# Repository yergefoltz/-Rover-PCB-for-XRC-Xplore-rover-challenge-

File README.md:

# -Rover-PCB-for-XRC-Xplore-rover-challenge-
My first PCB made for rover challenge at my university was designed to connect all electronics in our small rover.

1.	Main Purpose:
I decided to design our PCB solely for connections and routing logic signals between our components. The power supply lines for the servo and DC motors will not run through the board in order to avoid significant electrical noise that could interfere with the operation of the logic components.
2.	Brain – Master – Slaves 
The Raspberry Pi will not be fully mounted on the PCB; only a header with 20 pins will be included.
The same approach will be used for the Arduino master.
For the Arduino slaves, there will be dedicated spots on the PCB, allowing them to be mounted and removed as needed.
This design choice was made to avoid wasting space on the board and to keep it compact.
An important clarification: the appropriate resistors have been placed on the PCB to ensure proper logic operation.
Pull-up resistors are used for UART, along with a voltage divider between the Arduino master and the other components to ensure correct signal transmission.

Some additional components were placed to make the work of arduinos proper:

The ferrite bead (FB1) filters high-frequency noise on the power line.
The 100nF capacitor suppresses fast voltage spikes near the Arduino.
The 4.7µF capacitor smooths slower voltage drops.
Together, they stabilize the power and reduce noise from motors and servos.
This setup helps prevent glitches and random resets.
3.	More about Slaves…
Overall, we will have four Arduino slaves, each with its own specific role. Slaves #1 and #2 will handle rover control. Each of them will receive signals from the master (which in turn receives them from the Raspberry Pi), and will control the motors in parallel pairs via a driver (left front & rear + right front & rear), as well as one servo motor each.
This approach was chosen to improve the rover’s turning performance, where the servo motors will be especially useful.
Slave #3 will be used as a mini controller for the robotic arm, managing five servo motors, as well as two additional servos used in the LiDAR system. In total, it will control seven servo motors.
A dedicated slave was assigned for this purpose to avoid overloading the system and adding extra strain to the other components.

The final slave, #4, will manage all the sensors in the system and transmit the data to the appropriate modules.

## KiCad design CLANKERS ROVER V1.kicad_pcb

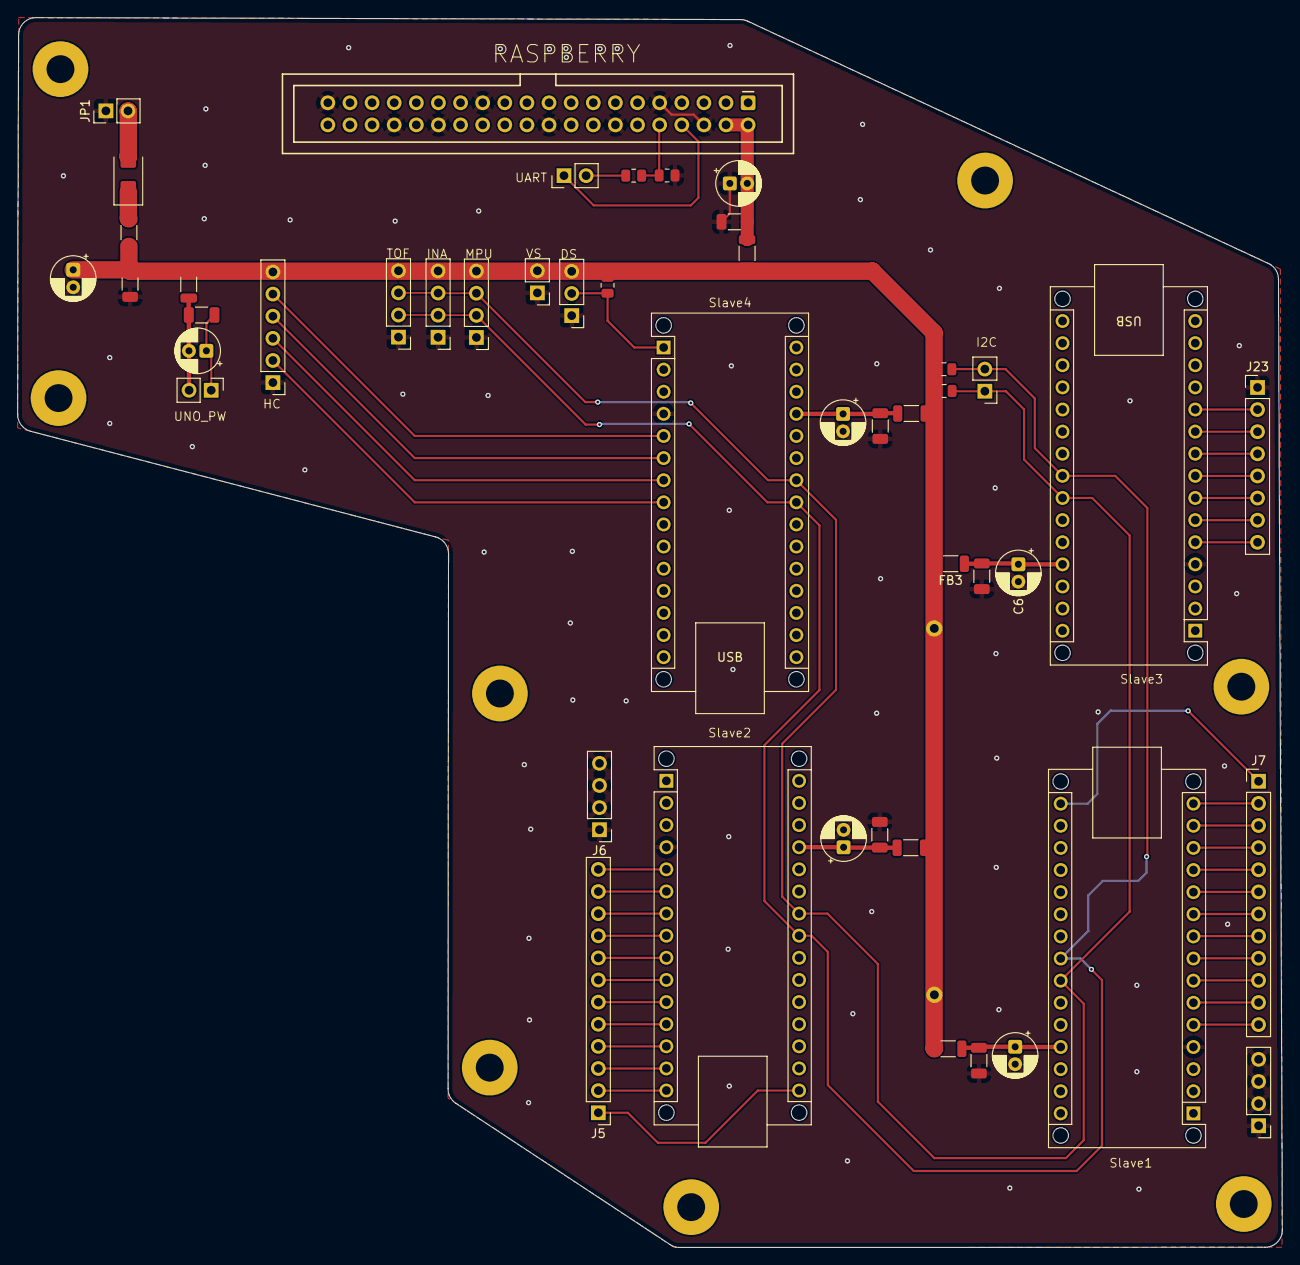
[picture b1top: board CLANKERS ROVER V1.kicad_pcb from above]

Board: 4 copper layers, 145.2 x 141.2 mm, 49 parts (0 on the bottom side), 52 nets.

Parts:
A1, A2: Arduino_Nano_v3.x; Arduino_Nano_WithMountingHoles
A3: Slave2; Arduino_Nano_WithMountingHoles
A4: Slave1; Arduino_Nano_WithMountingHoles
C1, C3, C4, C6, C11, C15, C16: 10uf; CP_Radial_D5.0mm_P2.00mm
C2, C5, C7, C8, C10, C14, C17: 100nf; C_1206_3216Metric
D1: SS23; D_SMA
FB1, FB2, FB3, FB4, FB5, FB6, FB8: 100; L_1206_3216Metric
I2CArdu_Uno1: Conn_01x02; PinHeader_1x02_P2.54mm_Vertical
J1: 2xHC-SR04P; PinHeader_1x06_P2.54mm_Vertical
J2: TOF; PinHeader_1x04_P2.54mm_Vertical
J3: INA3221; PinHeader_1x04_P2.54mm_Vertical
J4: 2xMPU6050; PinHeader_1x04_P2.54mm_Vertical
J5: Male_Connection 01x12 Slave 1; PinHeader_1x12_P2.54mm_Vertical
J6, J8: GND PINS; PinHeader_1x04_P2.54mm_Vertical
J7: Male_Connection 01x12 Slave 2; PinHeader_1x12_P2.54mm_Vertical
J9, J10: DRIVER 5V; 1x01_P2.54mm
J21: MPU 1vs2; PinHeader_1x02_P2.54mm_Vertical
J22: DS18B20; PinHeader_1x03_P2.54mm_Vertical
J23: 7 Servos; PinHeader_1x08_P2.54mm_Vertical
J32: Raspberry_Pi_2x20_PTH; 2x20_Shrouded
JP1: Conn_01x02 Male; PinHeader_1x02_P2.54mm_Vertical
PowerARDU_UNO1: Conn_01x02; PinHeader_1x02_P2.54mm_Vertical
R1: 4.7k; R_0805_2012Metric
R3, R5: 4.7K; R_0805_2012Metric
R7: 10k; R_0805_2012Metric
R10: 20k; R_0805_2012Metric
UART_ARDU_UNO_RASP1: Conn_01x02; PinHeader_1x02_P2.54mm_Vertical

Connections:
+5V: C16.1, C17.1, FB1.2, FB2.2, FB3.2, FB4.2, FB5.2, FB6.1, FB8.2, J1.6, J2.4, J3.4, J4.4, J9.1, J10.1, J21.2, J22.3, R1.1, R3.2, R5.2
/Slave 1 + Slave 2/AIN1: A3.10 (D7), J7.7
/Slave 1 + Slave 2/AIN1*: A4.10 (D7), J5.7
/Slave 1 + Slave 2/AIN2: A3.11 (D8), J7.6
/Slave 1 + Slave 2/AIN2*: A4.11 (D8), J5.6
/Slave 1 + Slave 2/BIN1: A3.13 (D10), J7.4
/Slave 1 + Slave 2/BIN1*: A4.13 (D10), J5.4
/Slave 1 + Slave 2/BIN2: A3.15 (D12), J7.2
/Slave 1 + Slave 2/BIN2*: A4.15 (D12), J5.2
/Slave 1 + Slave 2/ENCODER1B: A3.7 (D4), J7.10
/Slave 1 + Slave 2/ENCODER1B*: A4.7 (D4), J5.10
/Slave 1 + Slave 2/ENCODER2B: A3.16 (D13), J7.1
/Slave 1 + Slave 2/ENCODER2B*: A4.16 (D13), J5.1
/Slave 1 + Slave 2/ENC_1A_INT0: A3.5 (D2), J7.12
/Slave 1 + Slave 2/ENC_1A_INT0*: A4.5 (D2), J5.12
/Slave 1 + Slave 2/ENC_2A_INT1: A3.6 (D3), J7.11
/Slave 1 + Slave 2/ENC_2A_INT1*: A4.6 (D3), J5.11
/Slave 1 + Slave 2/PWR_MOTORB: A3.14 (D11), J7.3
/Slave 1 + Slave 2/PWR_MOTORB*: A4.14 (D11), J5.3
/Slave 1 + Slave 2/PW_A: A3.9 (D6), J7.8
/Slave 1 + Slave 2/PW_A*: A4.9 (D6), J5.8
/Slave 1 + Slave 2/SERVO_SL: A3.8 (D5), J7.9
/Slave 1 + Slave 2/SERVO_SL*: A4.8 (D5), J5.9
/Slave 1 + Slave 2/STBY: A3.12 (D9), J7.5
/Slave 1 + Slave 2/STBY*: A4.12 (D9), J5.5
/Slave 3/PWS 2: A2.6 (D3), J23.7
/Slave 3/PWS 3: A2.7 (D4), J23.6
/Slave 3/PWS 4: A2.8 (D5), J23.5
/Slave 3/PWS 5: A2.9 (D6), J23.4
/Slave 3/PWS 6: A2.10 (D7), J23.3
/Slave 3/PWS 7: A2.11 (D8), J23.2
/Slave 3/PWS SERVO_MOTOR_1: A2.5 (D2), J23.8
/Slave 4/D1/TX: A1.1 (D1/TX), J22.2, R1.2
/Slave 4/ECHO1: A1.6 (D3), J1.4
/Slave 4/ECHO2: A1.8 (D5), J1.2
/Slave 4/TRIG1: A1.5 (D2), J1.5
/Slave 4/TRIG2: A1.7 (D4), J1.3
/raspbery PI + Arduino Uno (Master)/D0_RX: J32.8 (GPIO14/TXD), UART_ARDU_UNO_RASP1.1
/raspbery PI + Arduino Uno (Master)/D1_RX: R7.1, UART_ARDU_UNO_RASP1.2
/raspbery PI + Arduino Uno (Master)/RXD: J32.10 (GPIO15/RXD), R7.2, R10.2
GND: A1.4 (GND), A2.4 (GND), A3.4 (GND), A4.4 (GND), C1.2, C2.2, C3.2, C4.2, C5.2, C6.2, C7.2, C8.2, C14.1, C15.1, C16.2, C17.2, J1.1, J2.1, J3.1, J4.1, J6.1, J6.2, J6.3, J6.4, J8.1, J8.2, J8.3, J8.4, J21.1, J22.1, J23.1, J32.6 (GND), J32.9 (GND), J32.14 (GND), J32.20 (GND), J32.25 (GND), J32.30 (GND), J32.34 (GND), J32.39 (GND), JP1.1, R10.1
unnamed: A1.27 (+5V), C4.1, C5.1, FB2.1
unnamed: A2.27 (+5V), C6.1, C7.1, FB3.1
unnamed: A3.27 (+5V), C1.1, C2.1, FB1.1
unnamed: A4.27 (+5V), C3.1, C8.1, FB4.1
unnamed: C14.2, C15.2, FB6.2, J32.2 (5V), J32.4 (5V)
unnamed: D1.2 (A), JP1.2
unnamed: D1.1 (K), FB8.1
unnamed: C10.1, C11.1, PowerARDU_UNO1.1
unnamed: C10.2, C11.2, FB5.1, PowerARDU_UNO1.2
SCL: A1.24 (A5), A2.24 (A5), A3.24 (A5), A4.24 (A5), I2CArdu_Uno1.1, J2.3, J3.3, J4.3, R5.1
SDA: A1.23 (A4), A2.23 (A4), A3.23 (A4), A4.23 (A4), I2CArdu_Uno1.2, J2.2, J3.2, J4.2, R3.1
